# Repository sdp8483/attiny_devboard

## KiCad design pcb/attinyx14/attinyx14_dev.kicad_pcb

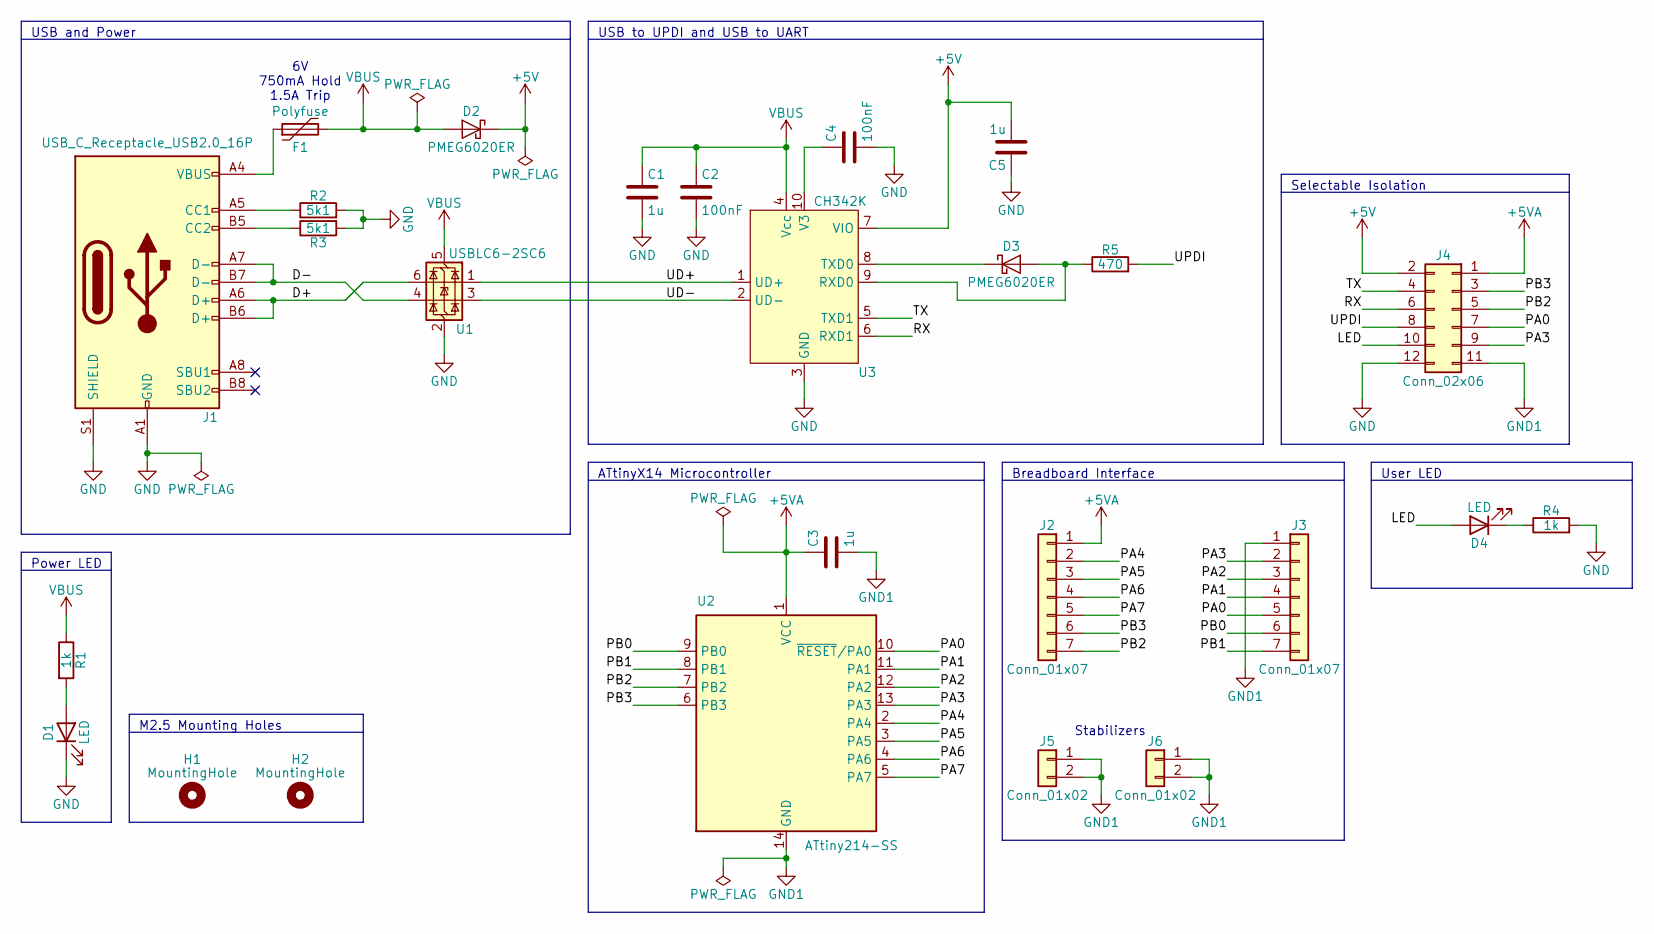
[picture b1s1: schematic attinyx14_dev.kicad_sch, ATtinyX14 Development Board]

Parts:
C1, C3, C5: 1u; C_0603_1608Metric; Voltage 16V; MPN FS18F105Z160PBG
C2, C4: 100nF; C_0603_1608Metric; Voltage 16V; MPN CL10B104KO8NNNC
D1, D4: LED; LED_0603_1608Metric; Voltage 1.6V-2.6V; MPN NCD0603R1
D2, D3: PMEG6020ER; Nexperia_CFP3_SOD-123W; Voltage 60V; MPN PMEG6020ER,115
F1: Polyfuse; Fuse_0805_2012Metric; Voltage 6V; MPN MF-PSMF075X-2
H1, H2: MountingHole; MountingHole_2.7mm_M2.5
J1: USB_C_Receptacle_USB2.0_16P; USB_C_Receptacle_G-Switch_GT-USB-7010ASV; Voltage 24V; MPN GT-USB-7010ASV
J2, J3: Conn_01x07; PinHeader_1x07_P2.54mm_Vertical; MPN IPCP254M07PB08V
J4: Conn_02x06; PinHeader_2x06_P2.54mm_Vertical; MPN IPCP254M12PB28V
J5, J6: Conn_01x02; PinHeader_1x02_P2.54mm_Vertical; MPN IPCP254M02PB08V
R1, R4: 1k; R_0603_1608Metric; Tolerance 5%; MPN RC1608J102CS
R2, R3: 5k1; R_0603_1608Metric; Tolerance 1%; MPN RC0603FR-075K1L
R5: 470; R_0805_2012Metric; Tolerance 1%; MPN RC0805FR-07470RL
U1: USBLC6-2SC6; SOT-23-6; Voltage 17V 6V; MPN USBLC6-2SC6
U2: ATtiny214-SS; SOIC-14_3.9x8.7mm_P1.27mm
U3: CH342K; SSOP-10-1EP_3.9x4.9mm_P1mm_EP2.1x3.3mm; MPN CH342K

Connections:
+5V: C5.2, D2.1 (K), J4.2, U3.7 (VIO)
+5VA: C3.1, J2.1, J4.1, U2.1 (VCC)
/D+: J1.A6 (D+), J1.B6 (D+), U1.6 (I/O1)
/D-: J1.A7 (D-), J1.B7 (D-), U1.4 (I/O2)
/LED: D4.2 (A), J4.10
/PA0: J3.5, J4.7, U2.10 (~RESET/PA0)
/PA1: J3.4, U2.11 (PA1)
/PA2: J3.3, U2.12 (PA2)
/PA3: J3.2, J4.9, U2.13 (PA3)
/PA4: J2.2, U2.2 (PA4)
/PA5: J2.3, U2.3 (PA5)
/PA6: J2.4, U2.4 (PA6)
/PA7: J2.5, U2.5 (PA7)
/PB0: J3.6, U2.9 (PB0)
/PB1: J3.7, U2.8 (PB1)
/PB2: J2.7, J4.5, U2.7 (PB2)
/PB3: J2.6, J4.3, U2.6 (PB3)
/RX: J4.6, U3.6 (RXD1)
/TX: J4.4, U3.5 (TXD1)
/UD+: U1.1 (I/O1), U3.1 (UD+)
/UD-: U1.3 (I/O2), U3.2 (UD-)
/UPDI: J4.8, R5.2
GND: C1.2, C2.2, C4.2, C5.1, D1.1 (K), J1.A1 (GND), J1.A12 (GND), J1.B1 (GND), J1.B12 (GND), J1.S1 (SHIELD), J4.12, R2.2, R3.2, R4.2, U1.2 (GND), U3.3 (GND), U3.11 (GND)
GND1: C3.2, J3.1, J4.11, J5.1, J5.2, J6.1, J6.2, U2.14 (GND)
unnamed: D1.2 (A), R1.2
unnamed: D3.2 (A), R5.1, U3.9 (RXD0)
unnamed: D3.1 (K), U3.8 (TXD0)
unnamed: D4.1 (K), R4.1
unnamed: F1.1, J1.A4 (VBUS), J1.A9 (VBUS), J1.B4 (VBUS), J1.B9 (VBUS)
unnamed: J1.A5 (CC1), R2.1
unnamed: J1.B5 (CC2), R3.1
unnamed: C4.1, U3.10 (V3)
VBUS: C1.1, C2.1, D2.2 (A), F1.2, R1.1, U1.5 (VBUS), U3.4 (Vcc)

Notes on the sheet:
Power LED
Selectable Isolation
ATtinyX14 Microcontroller
M2.5 Mounting Holes
USB to UPDI and USB to UART
Breadboard Interface
Stabilizers
User LED
USB and Power
6V 750mA Hold 1.5A Trip

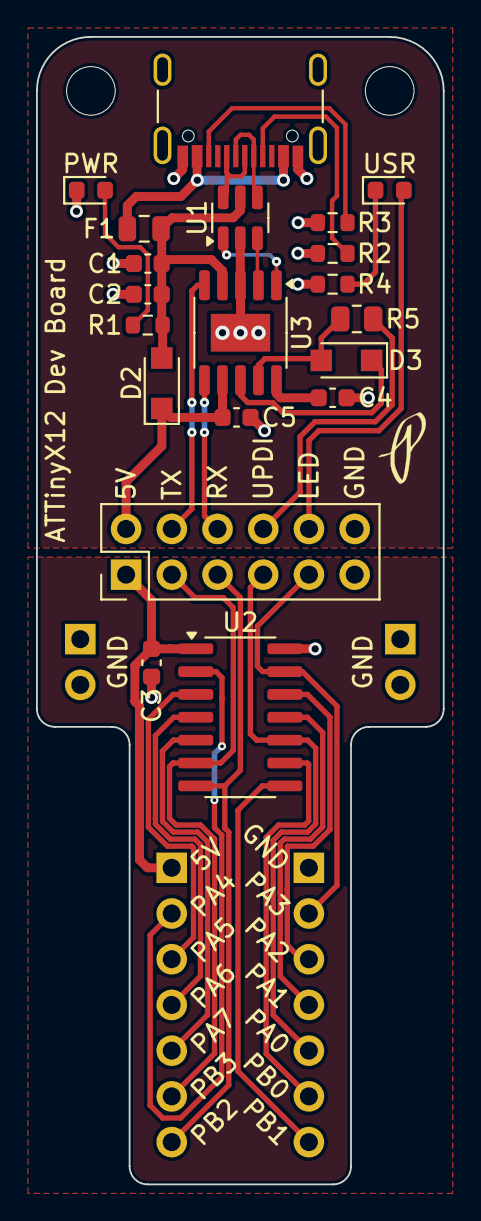
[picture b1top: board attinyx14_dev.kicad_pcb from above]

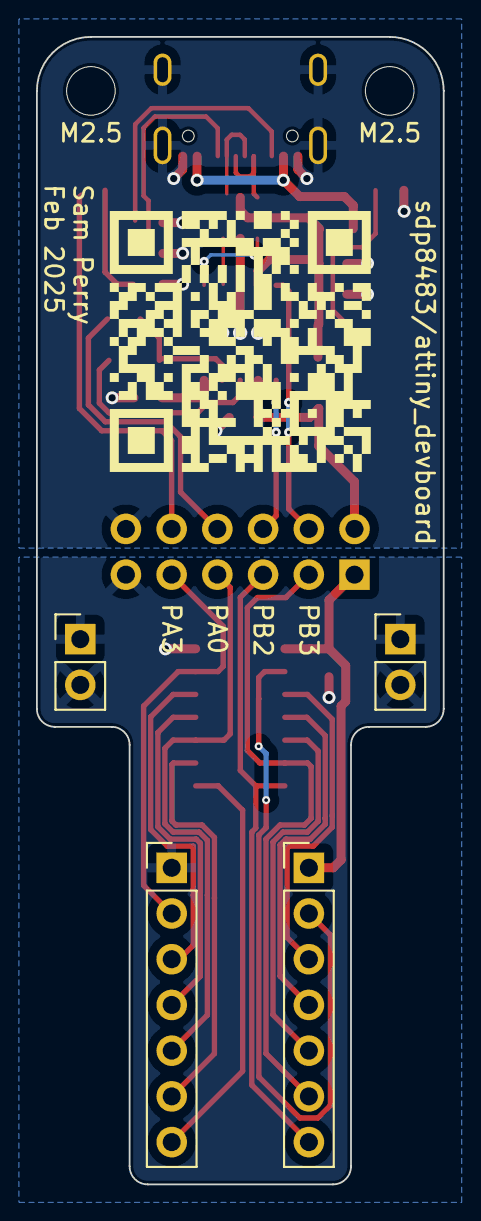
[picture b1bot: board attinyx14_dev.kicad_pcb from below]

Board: 2 copper layers, 22.6 x 63.8 mm, 27 parts (5 on the bottom side), 33 nets.

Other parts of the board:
QR*****: https://github.com/sdp8483/attiny_devboard; Github QR Code

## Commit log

2023-06-20 init commit
2023-06-21 start schma
2023-10-20 create
2024-06-28 resurect
2025-01-22 rename kicad project and dir
2025-01-23 schematic update
2025-01-24 add export script
2025-01-24 add datasheet
2025-01-24 Update sym-lib-table
2025-01-24 remove unused project specific symbol lib
2025-01-24 move USB pins
2025-01-24 create switch 3d model
2025-01-24 Create fp-lib-table
2025-01-24 schema done
2025-02-06 add mounting holes
2025-02-08 ignore auto_saved_files
2025-02-08 reduce mounting holes to 2.5mm
2025-02-08 replace switch with jumpers, remove buttons
2025-02-13 polyfuse and TVS+ESD for USB
2025-02-13 add power indicator LED
2025-02-13 TI Launchpad style isolation from programmer
2025-02-13 cleanup UPDI section
2025-02-13 flip isolation connector
2025-02-16 remove 2 mounting holes
2025-02-16 layout programmer side
2025-02-17 almost there
2025-02-17 user LED on programmer side
2025-02-21 rearrange layout
2025-02-22 add from cimos/Kicad-CustomDesignRules
2025-02-22 final layout
2025-02-22 add silkscreen
2025-02-23 export user drawings and comments
2025-02-23 add dimensions
2025-02-23 export from kicad
2025-02-23 adjustments after DFM analysis
2025-02-23 update components with MPN, SPN, etc
2025-02-23 export iBOM
2025-03-13 create blink example
2025-03-13 create uart hello world
2025-03-13 rename LED define
2025-03-13 add environments
2025-03-13 error using BAUD, change to BAUDRATE
2025-03-16 create pwm example
2025-04-18 pcb layout done
2025-04-18 drc check and fix
2025-04-18 add datasheet link
2025-04-18 update 3d model link
2025-04-18 export files
2025-04-22 start i2c lib
2025-04-23 update functions
2025-04-23 increment variable to see change in data stream
2025-04-24 test flow diagram
2025-04-24 rename and remove
2025-04-24 start i2c host read/write example
2025-04-25 trying to get read working
2025-04-25 new direction
2025-04-26 adding returns
2025-04-26 set sck using enum, cleanup comments and code
2025-04-26 move libs to separate repositories
2025-04-27 update for new sck set method
2025-04-29 use attiny libs from github repo
2025-04-29 use attiny libs from githb repo
